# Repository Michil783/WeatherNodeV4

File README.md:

# WeatherNodeV4

WeatherNode is a small HW device based on ESP8266 to capture actual weather conditions as temperature, pressure and humidity.
The data is send via Wifi to a MQTT broker.
The back office SW is stored in

https://github.com/Michil783/ClimateHist

The applications could run on a Raspberry Pi together with the MQTT broker.

For displaying the data I created a web page using the Astro framework based on an other github project.
More details could be found here: 

https://github.com/Michil783/weather-forecast

## Hardware

The hardware schema is done in KiCAD and could be found in https://github.com/michil783/WeatherNodeV4/PCB

As weather sensor the Arduino Sensor Board BMP280 is used. For battery charging and programming a USB-C connector is onboard.

The PCB layout is also done with KiCAD and could also be found in this folder.

After taking the meassurements it goes to a deep sleep for 15 minutes and restart again for the next meassurement.

With a 18650 LiIon battery with ~3500mAh capacity you get a working time up to 8-10 weeks before you need to recharge the battery.

### Details of the hardware

#### USB controller
The USB controller is a CH340C

#### Charging controller
For charging and battery controlling the LTC4054 is used. It is configured to use about 500mA.

#### Battery watching
To get the current state of charge and the battery voltage a MAX17048 chip is used. It provides all necessary information.

#### Weather Sensor
To get all necessary climate values the BOSCH BMP280 circuit from Arduino is used.

#### CPU
As CPU the ESP8266 board is used. Wifi and I2C interfaces are already onboard.

## Software

The system provides a Wifi AP for the first installation. The AP name is "WeatherNode-Wifi-Manager" with an IP of 192.168.4.1. Accessing this IP from a browser you get the manager to configure the WeatherNode into your Wifi and with a proper ID.

When the WeatherNode is used the first time and no settings are stored via the programming the Wifi Manager starts automatically.

Via the DIP switches you could reset these settings on the board and restart the Wifi Manager.
With DIP switch 2 you do a reset and DIP switch 1 is starting the Wifi Manager without reseting the data.

When settings are available, the node starts up and is connectiong to the specified Wifi and to the MQTT broker. After this it initializes all components on the board and waits for 2 seconds before reading the data from the weather sensor. This is done to warmup the sensor to get a more precise measurement.

After taking the measurement it creates a JSON package and sends it to the MQTT broker.

If transmission of packet is successful it goes to a deep sleep for 15 minutes and the cycle begins again with a restart of the node.

## Housing

In the folder Box is a construction for a box for the WeatherNode including space for a 18650 battery.

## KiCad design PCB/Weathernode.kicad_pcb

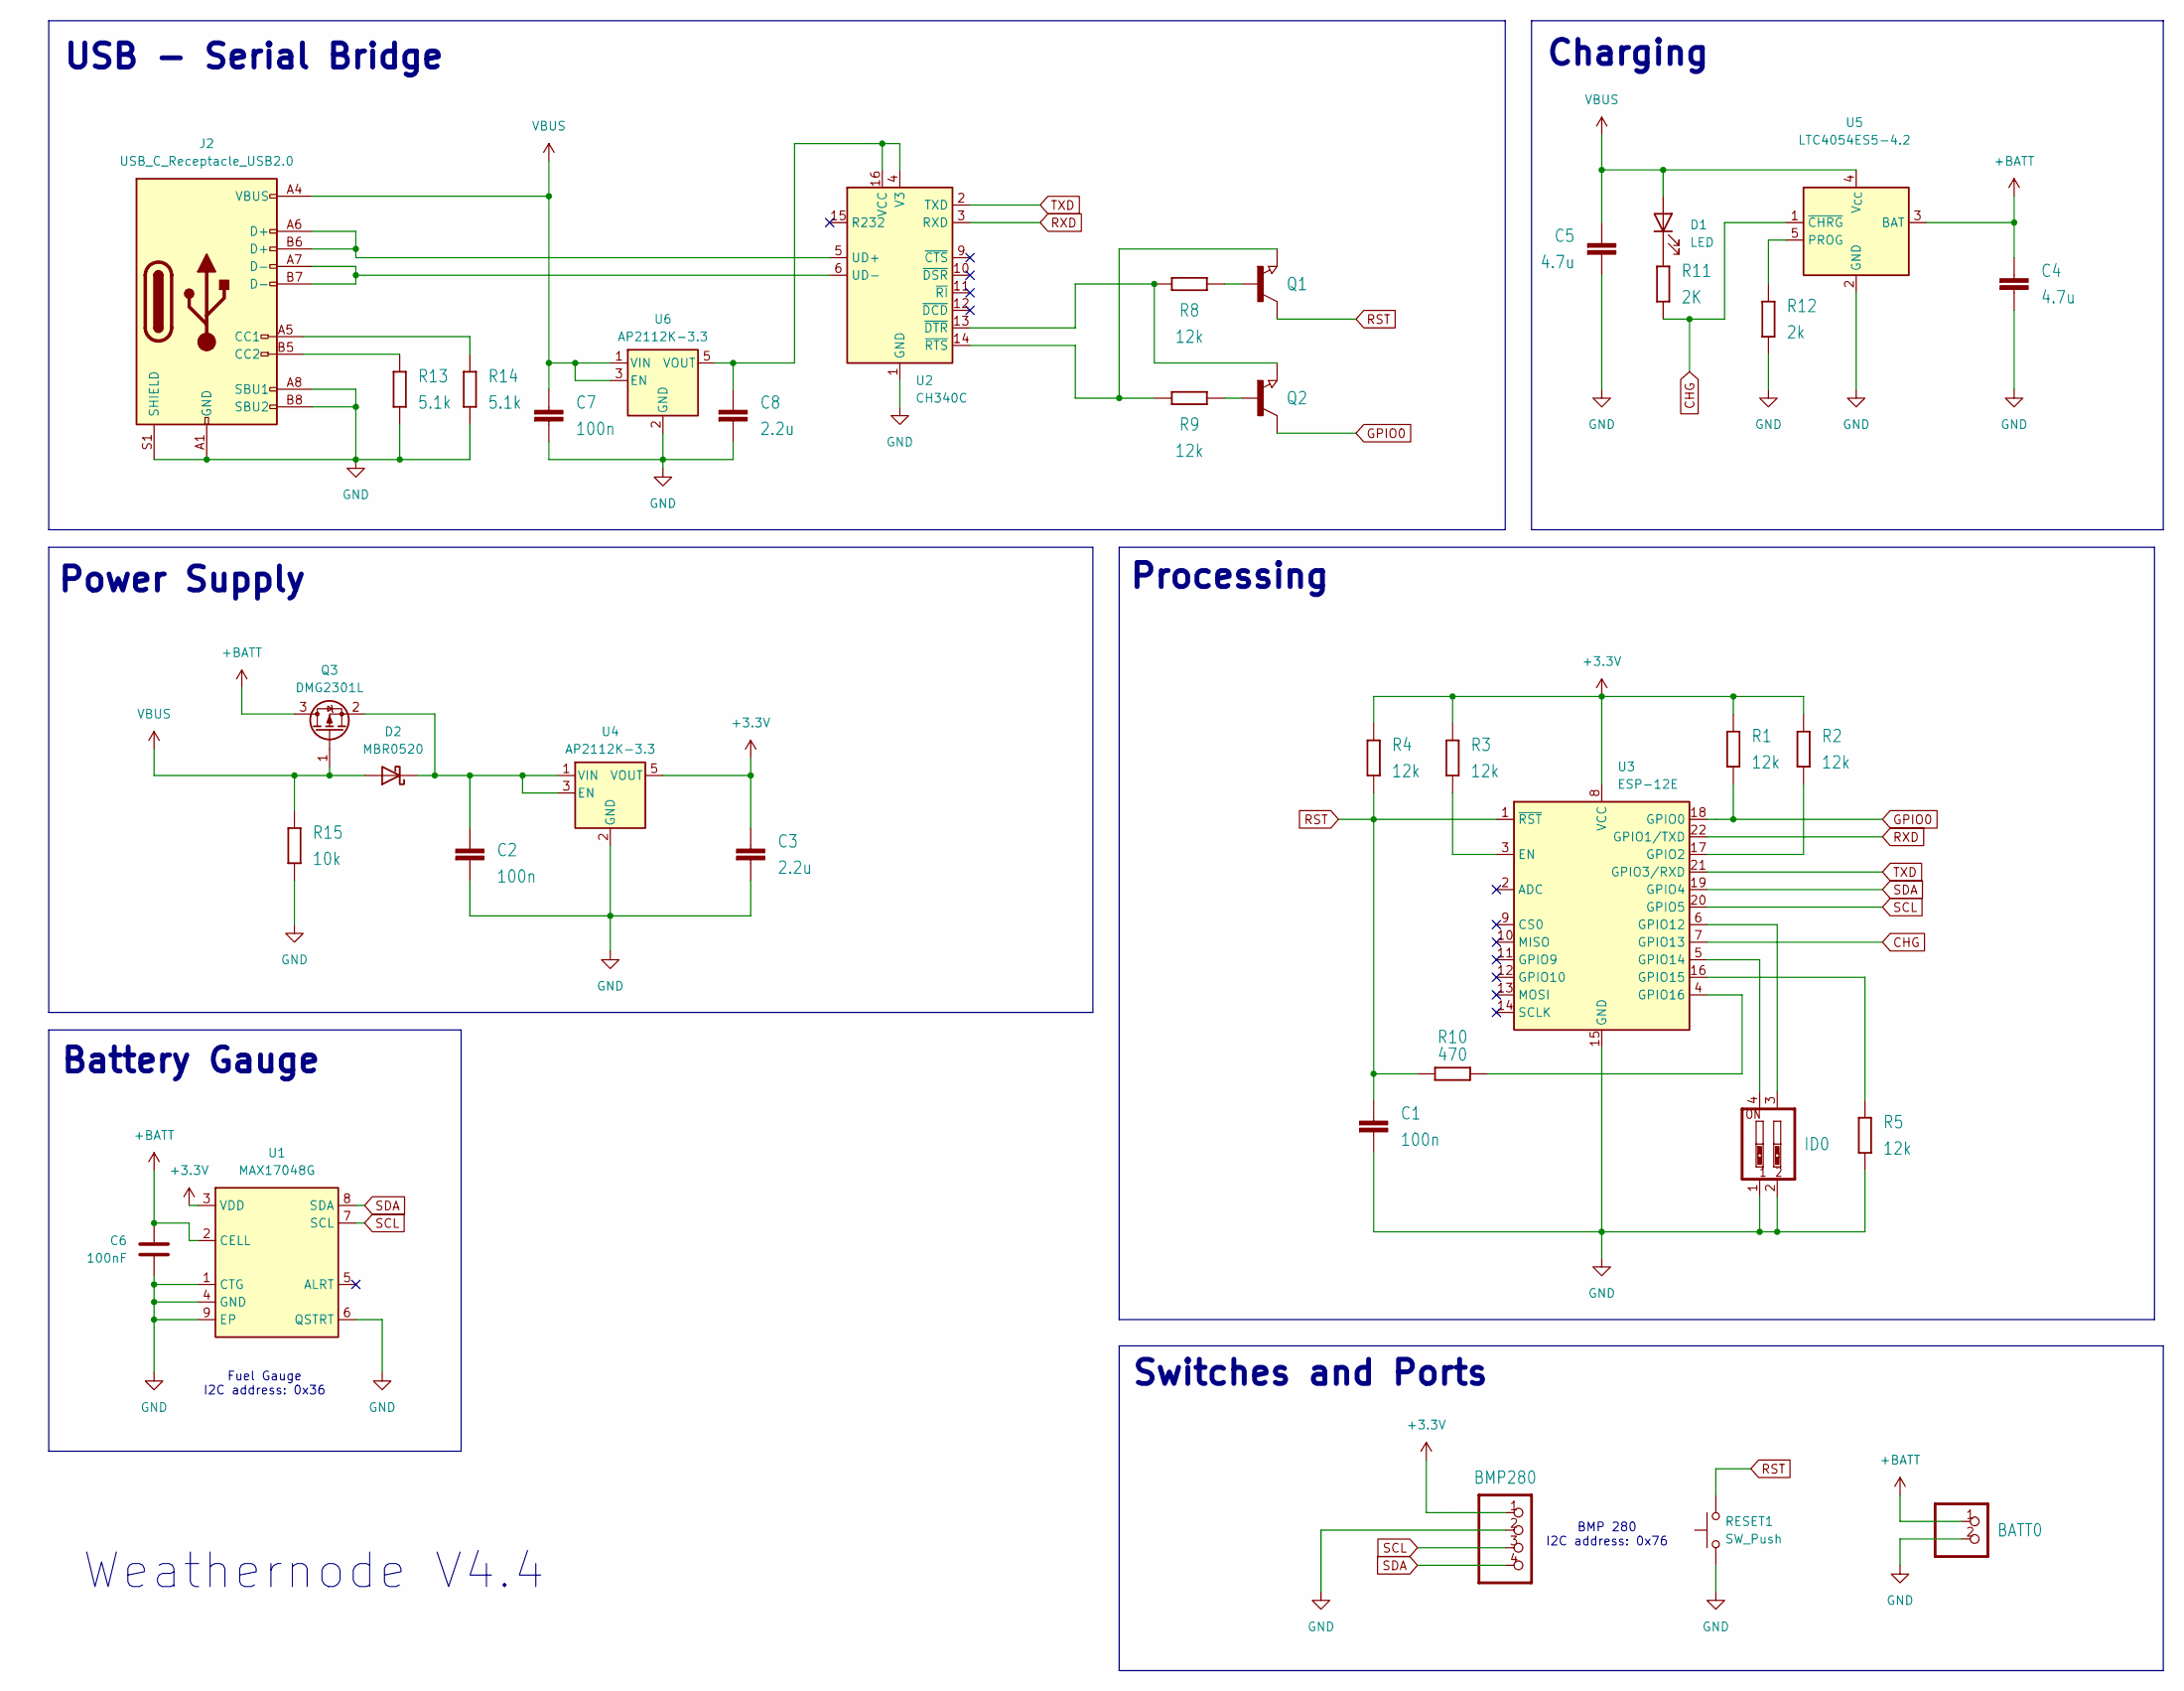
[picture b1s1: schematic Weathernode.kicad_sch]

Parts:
BATT0: PINHD-1X2; JST_B2B-PH-SM4-TB
BMP280: PINHD-1X4; PinHeader_1x04_P2.54mm_Vertical
C1, C2, C7: 100n; C_1206_3216Metric
C3, C8: 2.2u; C_1206_3216Metric
C4, C5: 4.7u; C_1206_3216Metric
C6: 100nF; C_1206_3216Metric; LCSC C1591
D1: LED; LED_1206_3216Metric
D2: MBR0520; D_SOD-123
ID0: SW_DIP-2; SW_DIP_SPSTx02_Slide_6.7x6.64mm_W6.73mm_P2.54mm_LowProfile_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
J2: USB_C_Receptacle_USB2.0; USB_C_Receptacle_HRO_TYPE-C-31-M-12
Q1, Q2: NPN-TRANSISTOR_SOT23; SOT-23-3
Q3: DMG2301L; SOT-23
R1, R2, R3, R4, R5, R8, R9: 12k; R_1206_3216Metric
R10: 470; R_1206_3216Metric
R11: 2K; R_1206_3216Metric
R12: 2k; R_1206_3216Metric
R13, R14: 5.1k; R_1206_3216Metric
R15: 10k; R_1206_3216Metric
RESET1: SW_Push; SW_SPST_TL3342
U1: MAX17048G; TDFN-8-1EP_2x2mm_P0.5mm_EP0.8x1.2mm; LCSC C2682616
U2: CH340C; SOIC-16_3.9x9.9mm_P1.27mm
U3: ESP-12E
U4, U6: AP2112K-3.3; SOT-23-5
U5: LTC4054ES5-4.2; TSOT-23-5

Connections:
CHG: R11.1, U3.7 (GPIO13), U5.1 (~CHRG)
GND: BATT0.2, BMP280.2, C1.2, C2.2, C3.2, C4.2, C5.2, C6.2, C7.2, C8.2, ID0.1, ID0.2, J2.A1 (GND), J2.A8 (SBU1), J2.A12 (GND), J2.B1 (GND), J2.B8 (SBU2), J2.B12 (GND), J2.S1 (SHIELD), R5.2, R12.1, R13.2, R14.2, R15.2, RESET1.1, U1.1 (CTG), U1.4 (GND), U1.6 (QSTRT), U1.9 (EP), U2.1 (GND), U3.15 (GND), U4.2 (GND), U5.2 (GND), U6.2 (GND)
GPIO0: Q2.3 (C), R1.1, U3.18 (GPIO0)
unnamed: D1.1 (K), R11.2
unnamed: C2.1, D2.1 (K), Q3.2 (S), U4.1 (VIN), U4.3 (EN)
unnamed: J2.A5 (CC1), R14.1
unnamed: J2.B5 (CC2), R13.1
unnamed: Q1.1 (B), R8.1
unnamed: Q1.2 (E), R9.2, U2.14 (~RTS)
unnamed: Q2.1 (B), R9.1
unnamed: Q2.2 (E), R8.2, U2.13 (~DTR)
unnamed: J2.A6 (D+), J2.B6 (D+), U2.5 (UD+)
unnamed: J2.A7 (D-), J2.B7 (D-), U2.6 (UD-)
unnamed: C8.1, U2.4 (V3), U2.16 (VCC), U6.5 (VOUT)
unnamed: R3.2, U3.3 (EN)
unnamed: R2.1, U3.17 (GPIO2)
unnamed: ID0.3, U3.6 (GPIO12)
unnamed: ID0.4, U3.5 (GPIO14)
unnamed: R5.1, U3.16 (GPIO15)
unnamed: R10.2, U3.4 (GPIO16)
unnamed: R12.2, U5.5 (PROG)
RST: C1.1, Q1.3 (C), R4.2, R10.1, RESET1.2, U3.1 (~RST)
RXD: U2.3 (RXD), U3.22 (GPIO1/TXD)
SCL: BMP280.3, U1.7 (SCL), U3.20 (GPIO5)
SDA: BMP280.4, U1.8 (SDA), U3.19 (GPIO4)
TXD: U2.2 (TXD), U3.21 (GPIO3/RXD)
VBUS: C5.1, C7.1, D1.2 (A), D2.2 (A), J2.A4 (VBUS), J2.A9 (VBUS), J2.B4 (VBUS), J2.B9 (VBUS), Q3.1 (G), R15.1, U5.4 (V_{CC}), U6.1 (VIN), U6.3 (EN)

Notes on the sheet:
Weathernode V4.4
Power Supply
BMP 280 I2C address: 0x76
Switches and Ports
Fuel Gauge I2C address: 0x36
Charging
Processing
Battery Gauge
USB - Serial Bridge

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
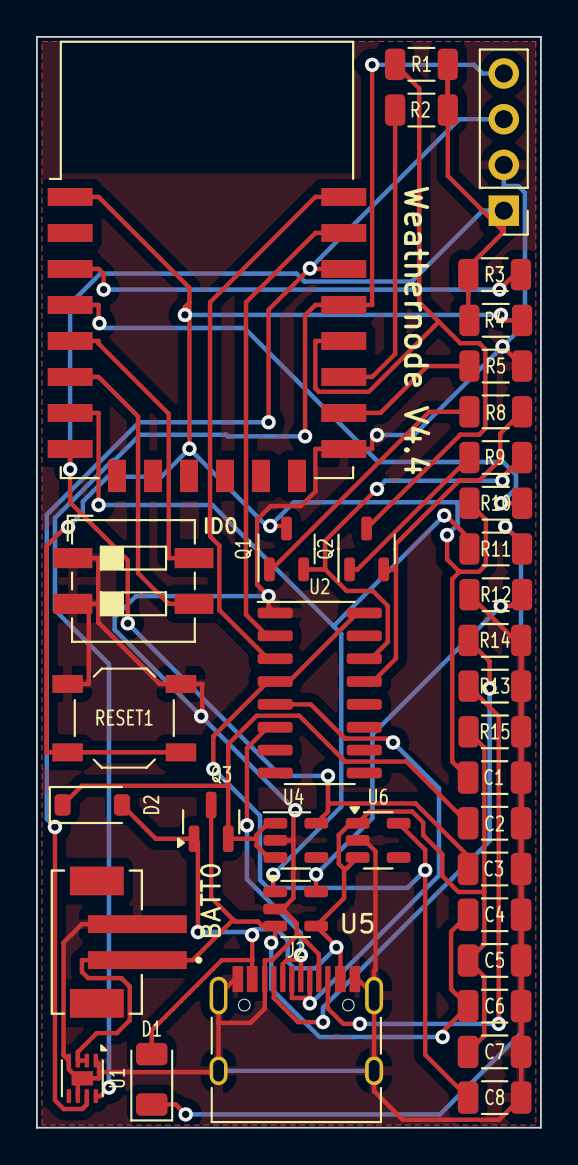
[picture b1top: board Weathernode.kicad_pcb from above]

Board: 2 copper layers, 28.0 x 60.6 mm, 37 parts (0 on the bottom side), 29 nets.

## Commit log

2025-08-24 general updates
2026-02-03 latest changes
2026-02-03 documentation
